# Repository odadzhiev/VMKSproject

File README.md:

# VMKSproject

Rocky е мултифункционална хоби ракета, която ще събира данни чрез сензори. Ракетата ще има парашут, ще може да се използва многократно и ще се управлява с дистанционно.

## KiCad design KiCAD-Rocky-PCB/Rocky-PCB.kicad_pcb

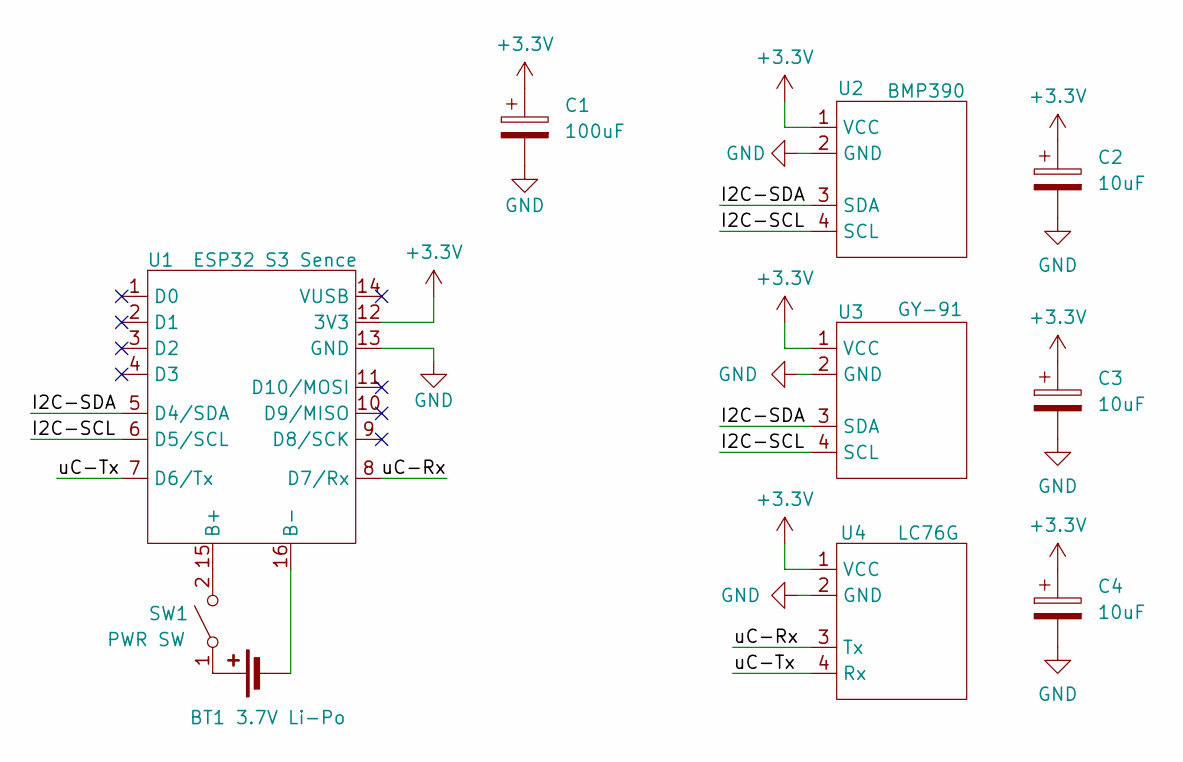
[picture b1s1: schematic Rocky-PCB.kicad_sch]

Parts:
BT1: 3.7V Li-Po; JST_XH_B2B-XH-AM_1x02_P2.50mm_Vertical
C1: 100uF; CP_Radial_Tantal_D5.5mm_P2.50mm
C2, C3, C4: 10uF; CP_Radial_Tantal_D4.5mm_P2.50mm
SW1: PWR SW; DIP4-SW
U1: ESP32 S3 Sence; XIAO-ESP32-S3-Sence
U2: BMP390; JST_XH_B4B-XH-A_1x04_P2.50mm_Vertical
U3: GY-91; JST_XH_B4B-XH-A_1x04_P2.50mm_Vertical
U4: LC76G; JST_XH_B4B-XH-A_1x04_P2.50mm_Vertical

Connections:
+3.3V: C1.1, C2.1, C3.1, C4.1, U1.12 (3V3), U2.1 (VCC), U3.1 (VCC), U4.1 (VCC)
/I2C-SCL: U1.6 (D5/SCL), U2.4 (SCL), U3.4 (SCL)
/I2C-SDA: U1.5 (D4/SDA), U2.3 (SDA), U3.3 (SDA)
/uC-Rx: U1.8 (D7/Rx), U4.3 (Tx)
/uC-Tx: U1.7 (D6/Tx), U4.4 (Rx)
GND: C1.2, C2.2, C3.2, C4.2, U1.13 (GND), U2.2 (GND), U3.2 (GND), U4.2 (GND)
unnamed: BT1.1 (+), SW1.1 (A)
unnamed: BT1.2 (-), U1.16 (B-)
unnamed: SW1.2 (B), U1.15 (B+)

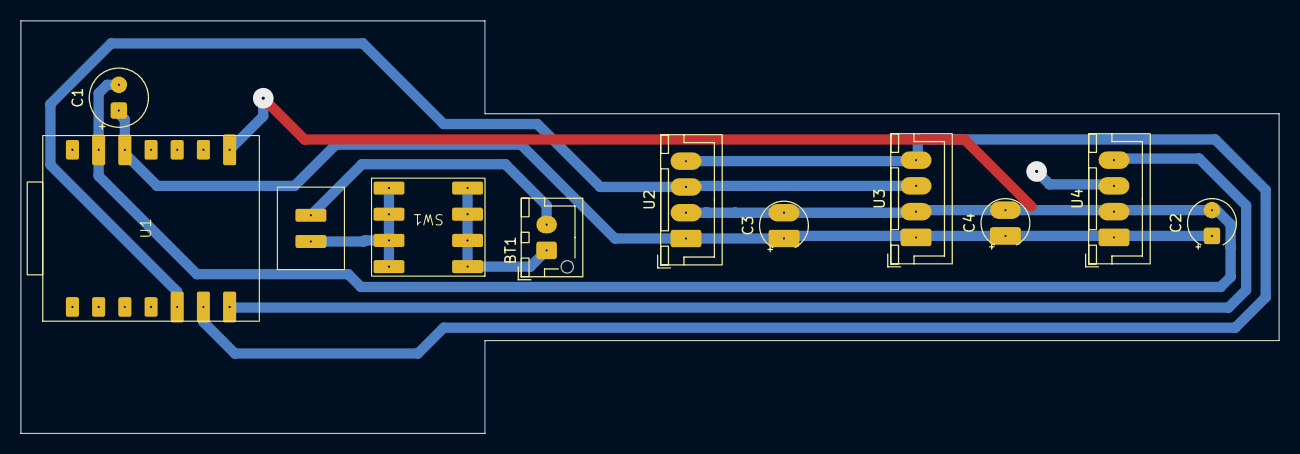
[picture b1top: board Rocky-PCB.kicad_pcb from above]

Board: 2 copper layers, 122.0 x 40.0 mm, 10 parts (0 on the bottom side), 9 nets.

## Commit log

2025-10-26 Add project description to README
    Added a project description in Bulgarian.
2026-03-31 ESP32 Receiver initial code
2026-03-31 Esp_sender code
2026-03-31 BPM390
2026-03-31 Created KiCAD Files
2026-03-31 Updated Files Paths
2026-03-31 Updated File Paths (Again)
2026-03-31 Removed files not needed in this branch
2026-03-31 Deleted Unneeded File
2026-04-02 Receiving data from sensor
2026-04-02 Sending data 2.0
2026-04-13 ONLY GY - 91
    code without BMP390
2026-04-13 GY - 91 and BMP390
2026-04-13 only GPS Module
2026-04-13 Sensors
2026-04-13 OpenRocket-Sims
2026-04-13 3D-Files
2026-04-14 Schematic and Sym lib
2026-04-14 Schematic Image
2026-04-14 Fixed pins for the different ESP
2026-04-14 Delete
2026-04-14 Wrong
2026-04-14 Update AllSensors.ino
    Removed commented setup line for BMP390.
2026-04-14 basic website
2026-04-14 updating receiver code
2026-04-14 Added Wireless Communication
2026-04-14 Added Wireless Comms
2026-04-14 presentation
2026-04-14 Rearranged files into foldeers
2026-04-14 Fixed Folder Naming
2026-04-14 Fixed folder naming ..again
2026-04-14 Added filtering capacitor and fixed some errors
2026-04-14 Added new filtering capacitors and added a picture of the schematic
2026-04-14 Fixed schematic image
2026-04-14 Cleaned up the unused files
2026-04-14 Added ESP32 wireless camera test code
2026-04-19 reflecting correct sensors in the site
2026-04-19 adding map
2026-04-19 firebase inclusion
2026-04-19 update ids
2026-04-19 design change satelites
2026-04-19 update design again
2026-04-19 map design
2026-04-19 backend inclusion, no firebase
2026-04-19 connection sensors and website by wifi
2026-04-19 Esp32 code for sending data to website over WiFi
2026-04-20 Create cam
2026-04-20 Added taking pictures and saving them to sd card
2026-04-23 PCB-V1
2026-04-23 PCB-V2
2026-04-24 Rocky-Pic
